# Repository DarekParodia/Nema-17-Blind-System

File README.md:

# Nema-17-Blind-System
I made my own system, for controling window blinds, using **Nema 17** stepper motor, and **a4988** stepper driver.
Design involves 3d printing, and making homemade pcb, or just using unviersal one.
Blinds can be easly controlled either by buttons or external hardware. PCB has 5 pins coming out of it, which has all the voltages and button pins coming in to microcontroller.
To connect motor to the pcb i used 2mm goldpins, because my motor has this type of connector.
You can drive blinds using gearbox, it depends on how heavy your blinds are, or how strong is your motor.
Design uses M3 screws to assembly everything. I didn't put points for screwing the pcb so you can attach it anyway you want

STL files can be found also on thingiverse: https://www.thingiverse.com/thing:5415491

# 🛠 Needed Parts
- 1x Nema 17 motor
- 1x a4988 driver
- Switches
    - 2x microswitch
    - 1x quad dip switch
- IC
    - 1x attiny 13
    - 1x lm7805
- Connectors
    - 1x quad goldpins (2mm)
    - 1x fivefold goldpins (2,54mm)
    - 1x dc jack (5.5mm)
- 2x capacitor (12v 100f)
- resistors
    -  2x 1 kΩ
    -  1x 470 Ω
- 1x 3mm led
- 1x 62x42 mm pcb  
- 12v power supply 1A (motor don't needs that much power but it's better to have more)
# 🔧 Assembly
- 3d print all needed parts
    - motor mount
    - blind holder
    - gearbox (Optional)
- screw motor to the motor mount (Optional: screw it with the gearbox)
- put on the tip blind holder
- screw all thing to the wall

# 🧩 Code
coming soon

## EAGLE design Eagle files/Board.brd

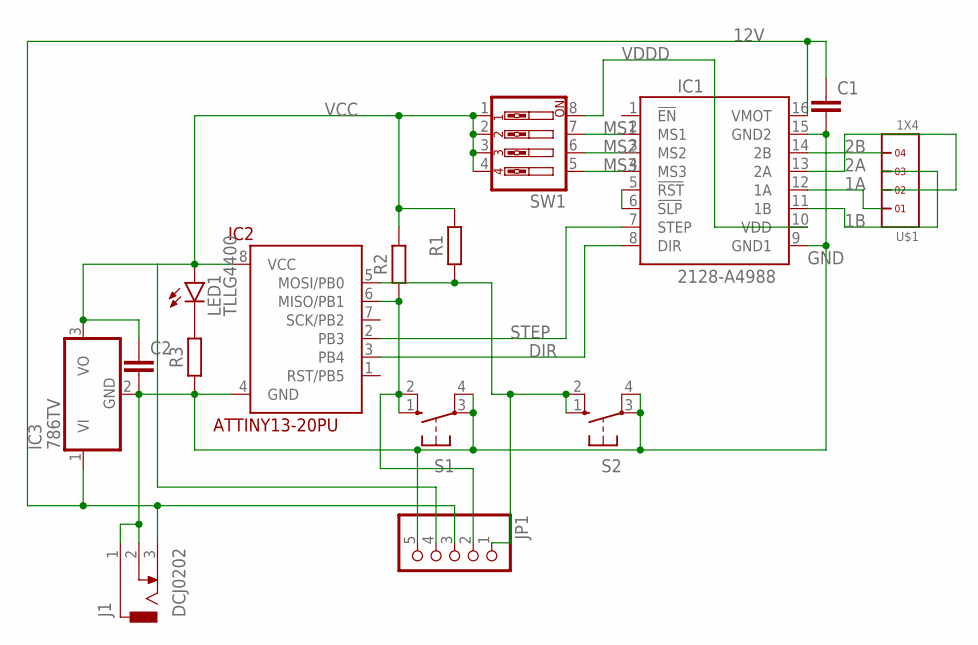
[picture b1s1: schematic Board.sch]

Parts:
C1, C2: C2.5/6; C2.5-6
IC1: 2128-A4988; A4988
IC2: ATTINY13-20PU; DIL08
IC3: 786TV; TO220V
J1: DCJ0202
JP1: PINHD-1X5; 1X05
LED1: TLLG4400; LED3MM
R1, R2, R3: R_AXIAL-7.2MM-PITCH; RESAD724W46L381D178B
S1, S2: 10-XX; B3F-10XX
SW1: SW_DIP-4; EDG-04
U$1: 1X4

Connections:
1A: IC1.12 (1A), U$1.1
1B: IC1.11 (1B), U$1.3
2A: IC1.13 (2A), U$1.2
2B: IC1.14 (2B), U$1.4
12V: C1.1, IC1.16 (VMOT), IC3.1 (VI), J1.3, JP1.3
DIR: IC1.8 (DIR), IC2.3 (PB4)
GND: C1.2, C2.2, IC1.9 (GND1), IC1.15 (GND2), IC2.4 (GND), IC3.2 (GND), J1.1, J1.2, JP1.5, R3.1, S1.3, S1.4 (P1), S2.3, S2.4 (P1)
MS1: IC1.2 (MS1), SW1.7
MS2: IC1.3 (MS2), SW1.6
MS3: IC1.4 (MS3), SW1.5
unnamed: LED1.K (C), R3.2
unnamed: IC2.5 (MOSI/PB0), JP1.1, R1.1, S2.1 (S), S2.2 (S1)
unnamed: IC1.5 (!RST), IC1.6 (!SLP)
PB1: IC2.6 (MISO/PB1), JP1.2, R2.1, S1.1 (S), S1.2 (S1)
STEP: IC1.7 (STEP), IC2.2 (PB3)
VCC: C2.1, IC2.8 (VCC), IC3.3 (VO), JP1.4, LED1.A, R1.2, R2.2, SW1.1, SW1.2, SW1.3, SW1.4
VDDD: IC1.10 (VDD), SW1.8

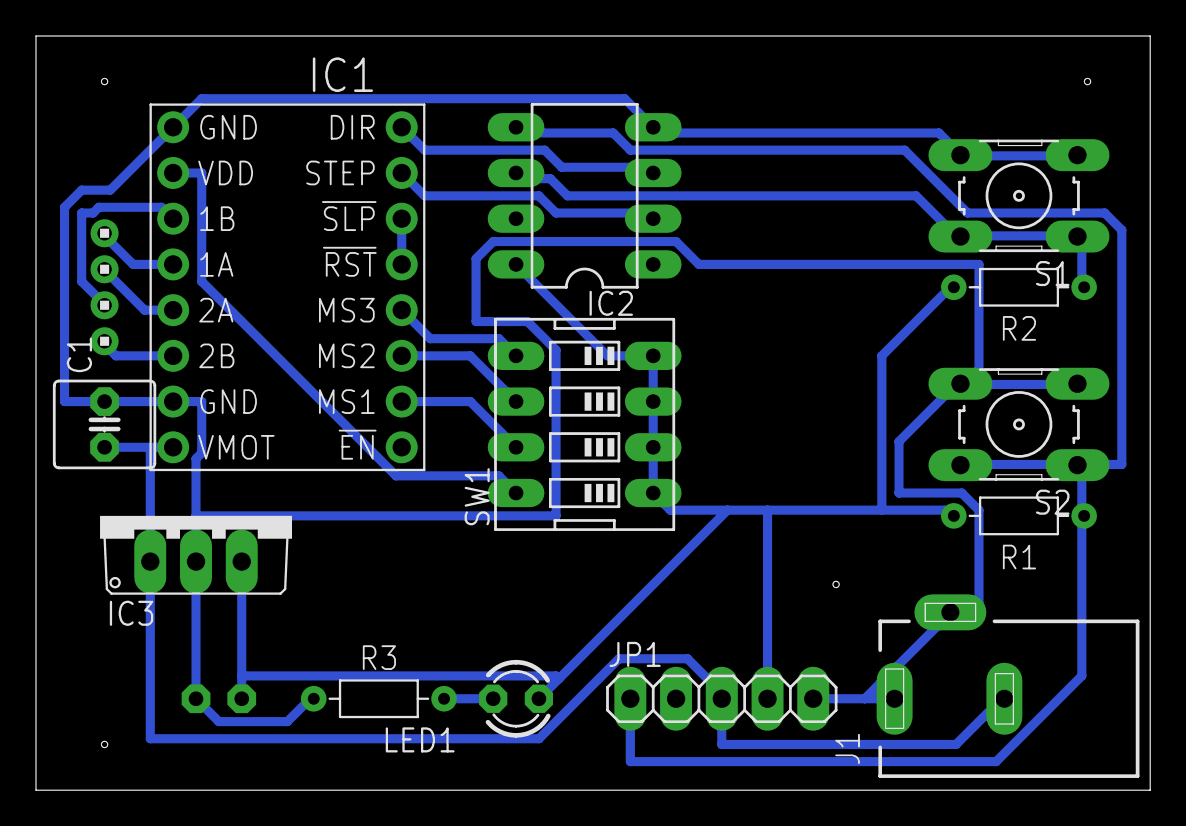
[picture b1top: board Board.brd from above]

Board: 2 copper layers, 61.9 x 41.9 mm, 15 parts (1 on the bottom side), 17 nets.

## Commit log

2022-06-20 Creating readme
2022-06-20 Update README.md
    added thingiverse link
